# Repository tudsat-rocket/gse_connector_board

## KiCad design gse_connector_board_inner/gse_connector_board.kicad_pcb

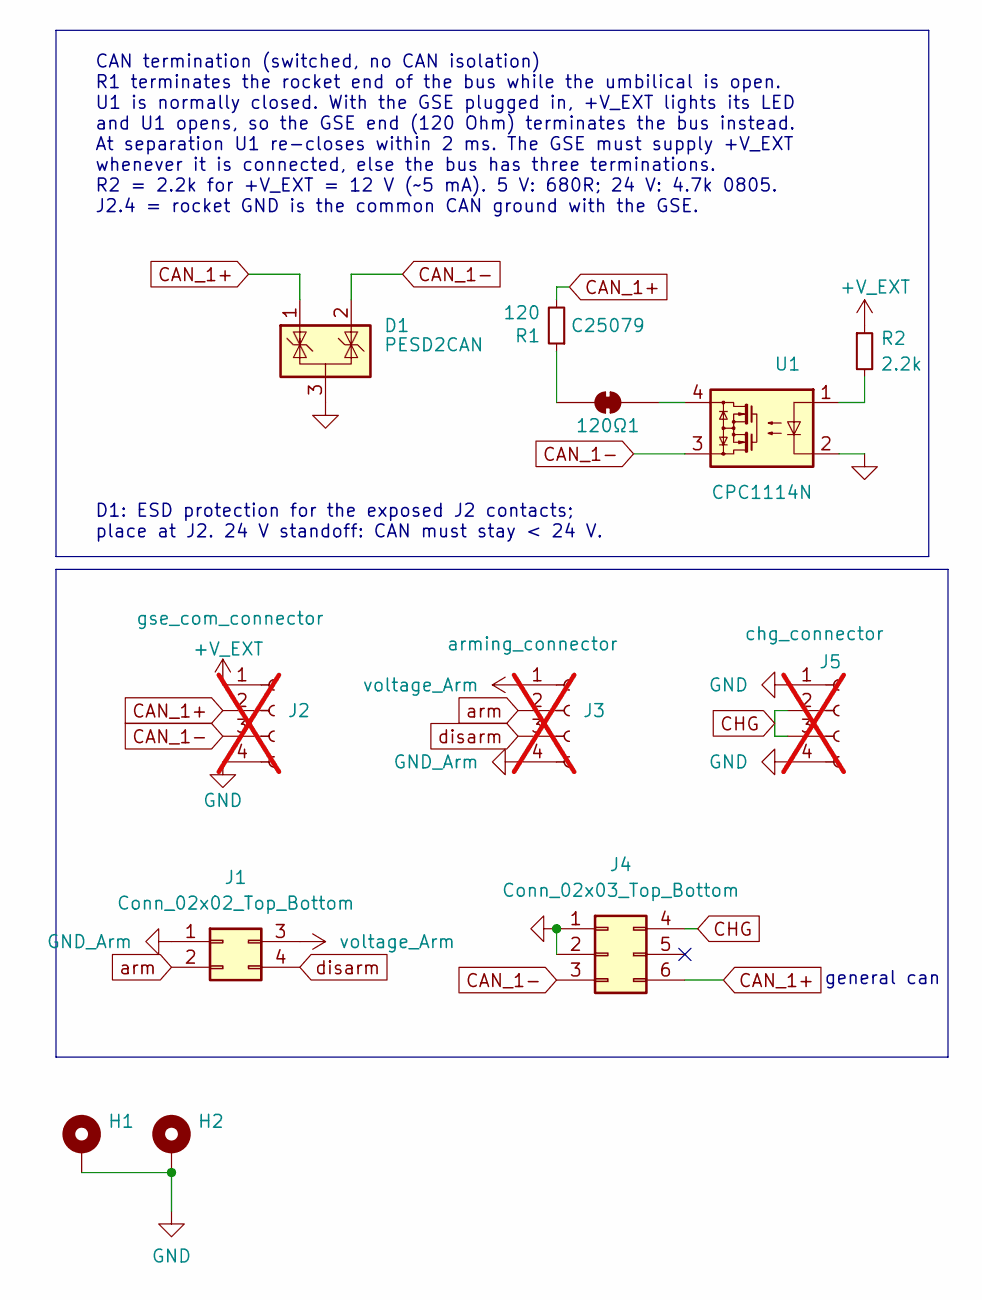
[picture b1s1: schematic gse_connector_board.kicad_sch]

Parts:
120Ω1: SolderJumper_2_Bridged; SolderJumper-2_P1.3mm_Bridged_RoundedPad1.0x1.5mm
D1: PESD2CAN; SOT-23; Part# PESD2CAN,215; LCSC C75176
H1, H2: MountingHole_Pad; MountingHole_3.2mm_M3_DIN965_Pad
J1: Conn_02x02_Top_Bottom; Molex_Micro-Fit_3.0_43045-0400_2x02_P3.00mm_Horizontal
J2: gse_com_connector; 4_pin_mag_con_mv_adapt; not fitted
J3: arming_connector; 4_pin_mag_con_mv_adapt; not fitted
J4: Conn_02x03_Top_Bottom; Molex_Micro-Fit_3.0_43045-0600_2x03_P3.00mm_Horizontal
J5: chg_connector; 4_pin_mag_con_mv_adapt; not fitted
R1: 120; R_0603_1608Metric_Pad0.98x0.95mm_HandSolder; LCSC C25079
R2: 2.2k; R_0603_1608Metric_Pad0.98x0.95mm_HandSolder; LCSC C4190
U1: CPC1114N; SOP-4_3.8x4.1mm_P2.54mm; LCSC C1558975

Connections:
+V_EXT: J2.1, R2.1
CAN_1+: D1.1 (K), J2.2, J4.6, R1.2
CAN_1-: D1.2 (K), J2.3, J4.3, U1.3
CHG: J4.4, J5.2, J5.3
GND: D1.3 (A), H1.1 (1_1), H2.1 (1_1), J2.4, J4.1, J4.2, J5.1, J5.4, U1.2
GND_Arm: J1.1, J3.4
unnamed: 120Ω1.1 (A), R1.1
unnamed: 120Ω1.2 (B), U1.4
unnamed: R2.2, U1.1
arm: J1.2, J3.2
disarm: J1.4, J3.3
voltage_Arm: J1.3, J3.1

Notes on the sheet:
CAN termination (switched, no CAN isolation) R1 terminates the rocket end of the bus while the umbilical is open. U1 is normally closed. With the GSE plugged in, +V_EXT lights its LED and U1 opens, so the GSE end (120 Ohm) terminates the bus instead. At separation U1 re-closes within 2 ms. The GSE 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
general can
D1: ESD protection for the exposed J2 contacts; place at J2. 24 V standoff: CAN must stay < 24 V.

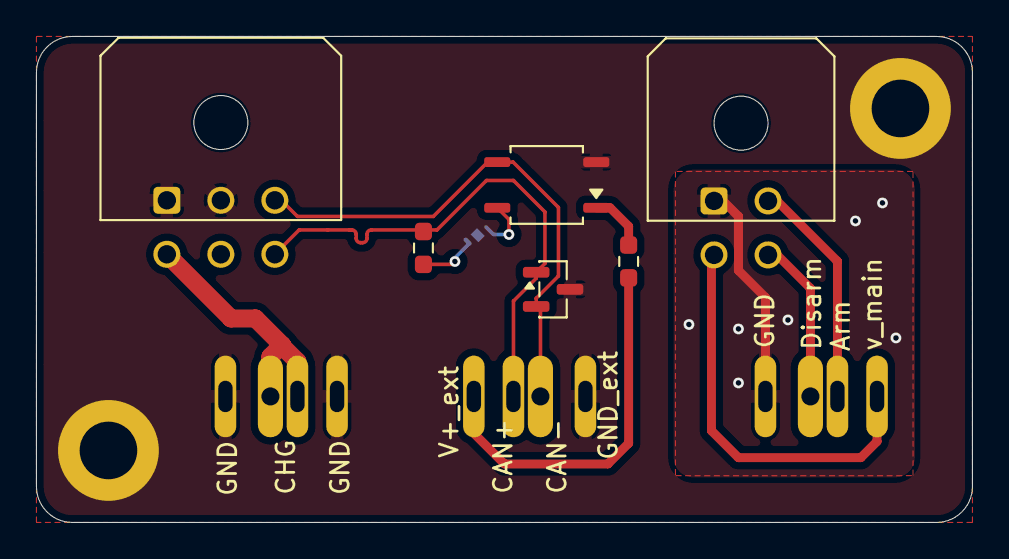
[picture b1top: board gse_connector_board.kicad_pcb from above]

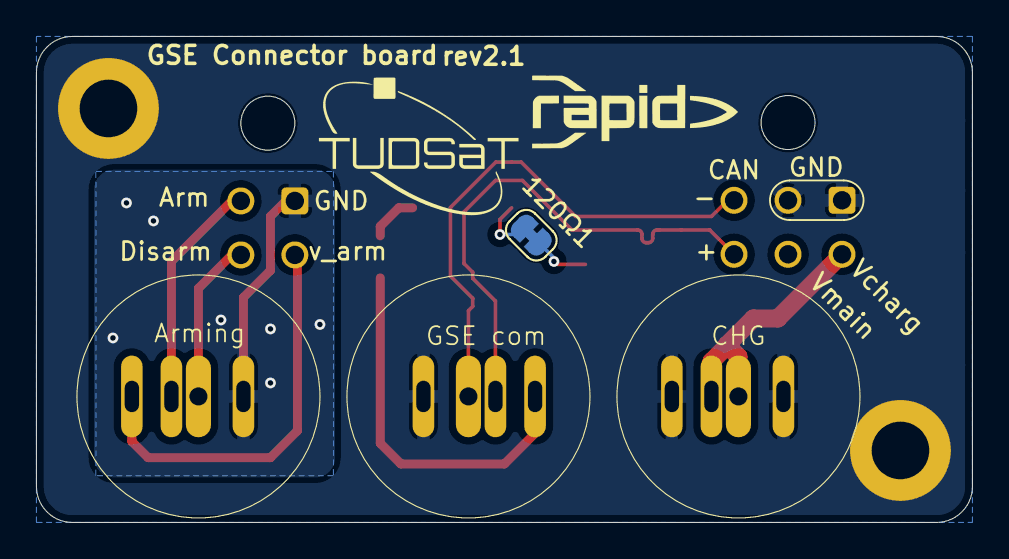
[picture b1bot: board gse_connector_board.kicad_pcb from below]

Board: 2 copper layers, 52.0 x 27.0 mm, 12 parts (4 on the bottom side), 12 nets.

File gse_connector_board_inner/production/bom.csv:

Designator,Footprint,Quantity,Value,LCSC Part #
D1,SOT-23,1,PESD2CAN,C75176
J1,Molex_Micro-Fit_3.0_43045-0400_2x02_P3.00mm_Horizontal,1,Conn_02x02_Top_Bottom,
J4,Molex_Micro-Fit_3.0_43045-0600_2x03_P3.00mm_Horizontal,1,Conn_02x03_Top_Bottom,
R1,0603,1,120,C25079
R2,0603,1,2.2k,C4190
U1,SOP-4_3.8x4.1mm_P2.54mm,1,CPC1114N,C1558975

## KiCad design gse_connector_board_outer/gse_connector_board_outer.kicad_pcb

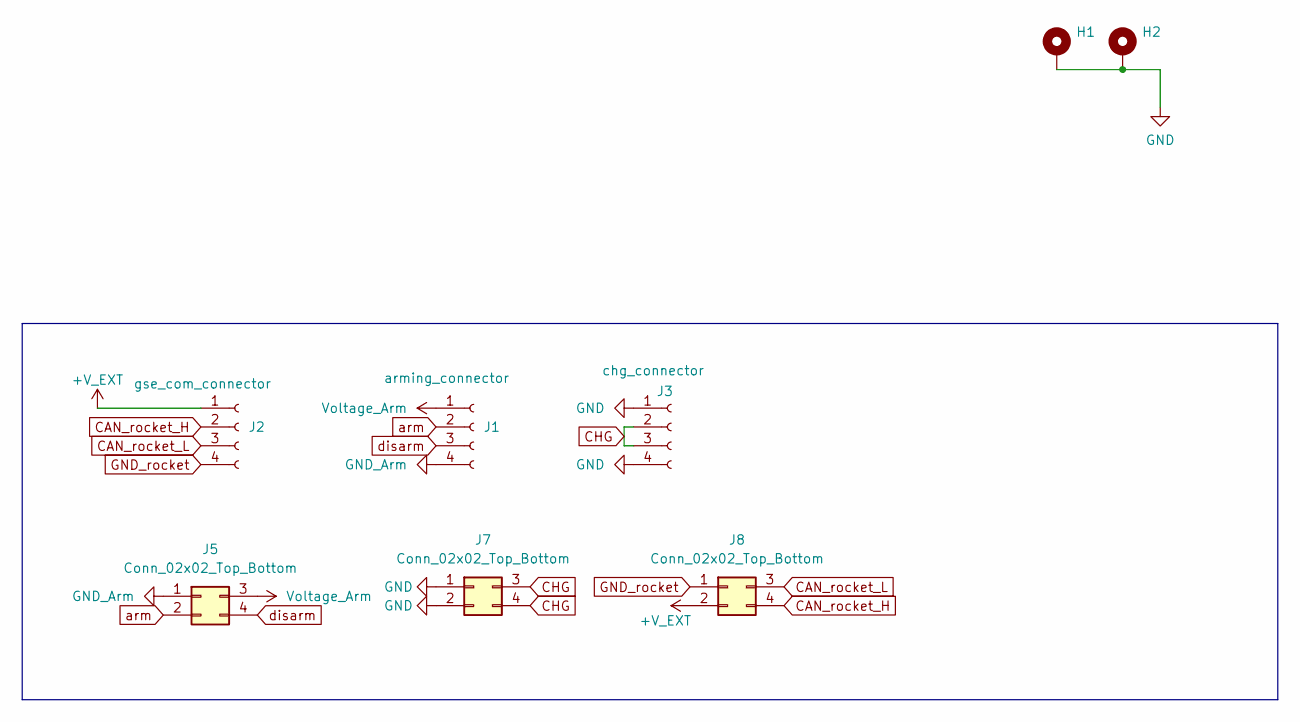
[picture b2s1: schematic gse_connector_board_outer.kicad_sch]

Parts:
H1, H2: MountingHole_Pad; MountingHole_3.2mm_M3_DIN965_Pad
J1: arming_connector; 4_pin_mag_con_flat_mv_adapt
J2: gse_com_connector; 4_pin_mag_con_flat_mv_adapt
J3: chg_connector; 4_pin_mag_con_flat_mv_adapt
J5, J7, J8: Conn_02x02_Top_Bottom; Molex_Micro-Fit_3.0_43045-0400_2x02_P3.00mm_Horizontal

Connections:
+V_EXT: J2.1, J8.2
CAN_rocket_H: J2.2, J8.4
CAN_rocket_L: J2.3, J8.3
CHG: J3.2, J3.3, J7.3, J7.4
GND: H1.1 (1_1), H2.1 (1_1), J3.1, J3.4, J7.1, J7.2
GND_Arm: J1.4, J5.1
GND_rocket: J2.4, J8.1
Voltage_Arm: J1.1, J5.3
arm: J1.2, J5.2
disarm: J1.3, J5.4

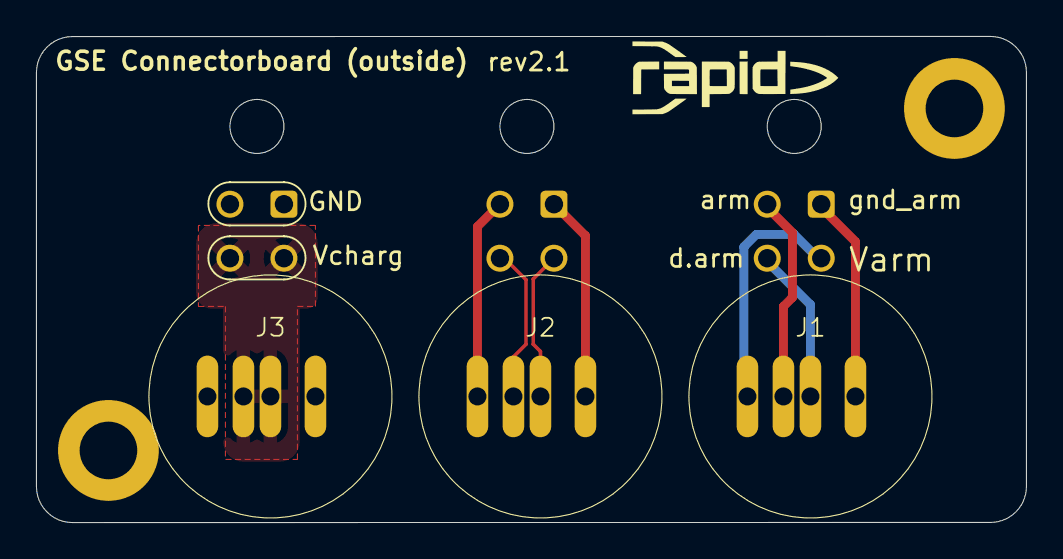
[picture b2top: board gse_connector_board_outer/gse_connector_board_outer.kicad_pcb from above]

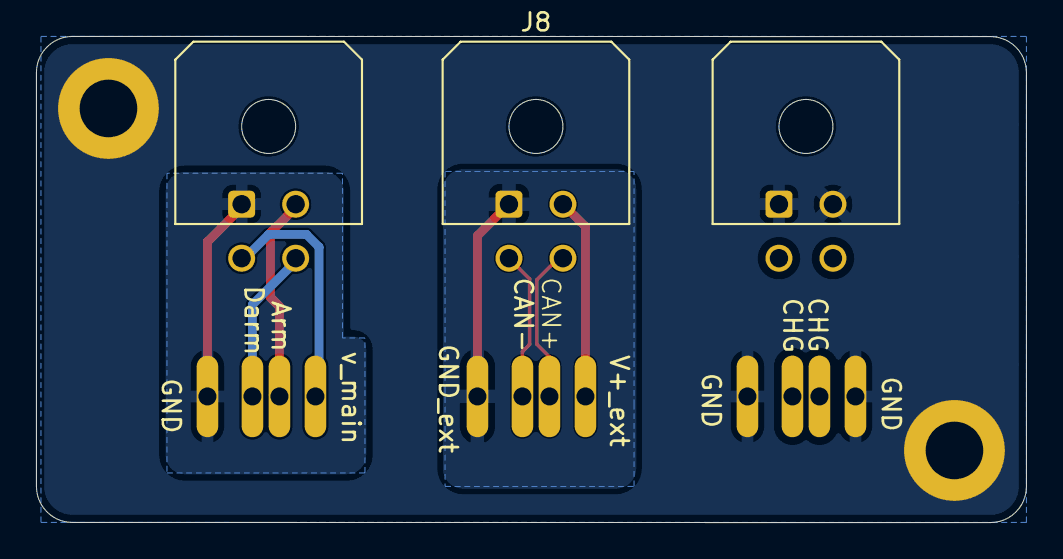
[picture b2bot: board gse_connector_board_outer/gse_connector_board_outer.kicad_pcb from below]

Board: 2 copper layers, 55.0 x 27.0 mm, 8 parts (3 on the bottom side), 10 nets.

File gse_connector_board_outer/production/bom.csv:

Designator,Footprint,Quantity,Value,LCSC Part #
J1,4_pin_mag_con_flat_mv_adapt,1,arming_connector,
J2,4_pin_mag_con_flat_mv_adapt,1,gse_com_connector,
J3,4_pin_mag_con_flat_mv_adapt,1,chg_connector,
"J5, J7, J8",Molex_Micro-Fit_3.0_43045-0400_2x02_P3.00mm_Horizontal,3,Conn_02x02_Top_Bottom,

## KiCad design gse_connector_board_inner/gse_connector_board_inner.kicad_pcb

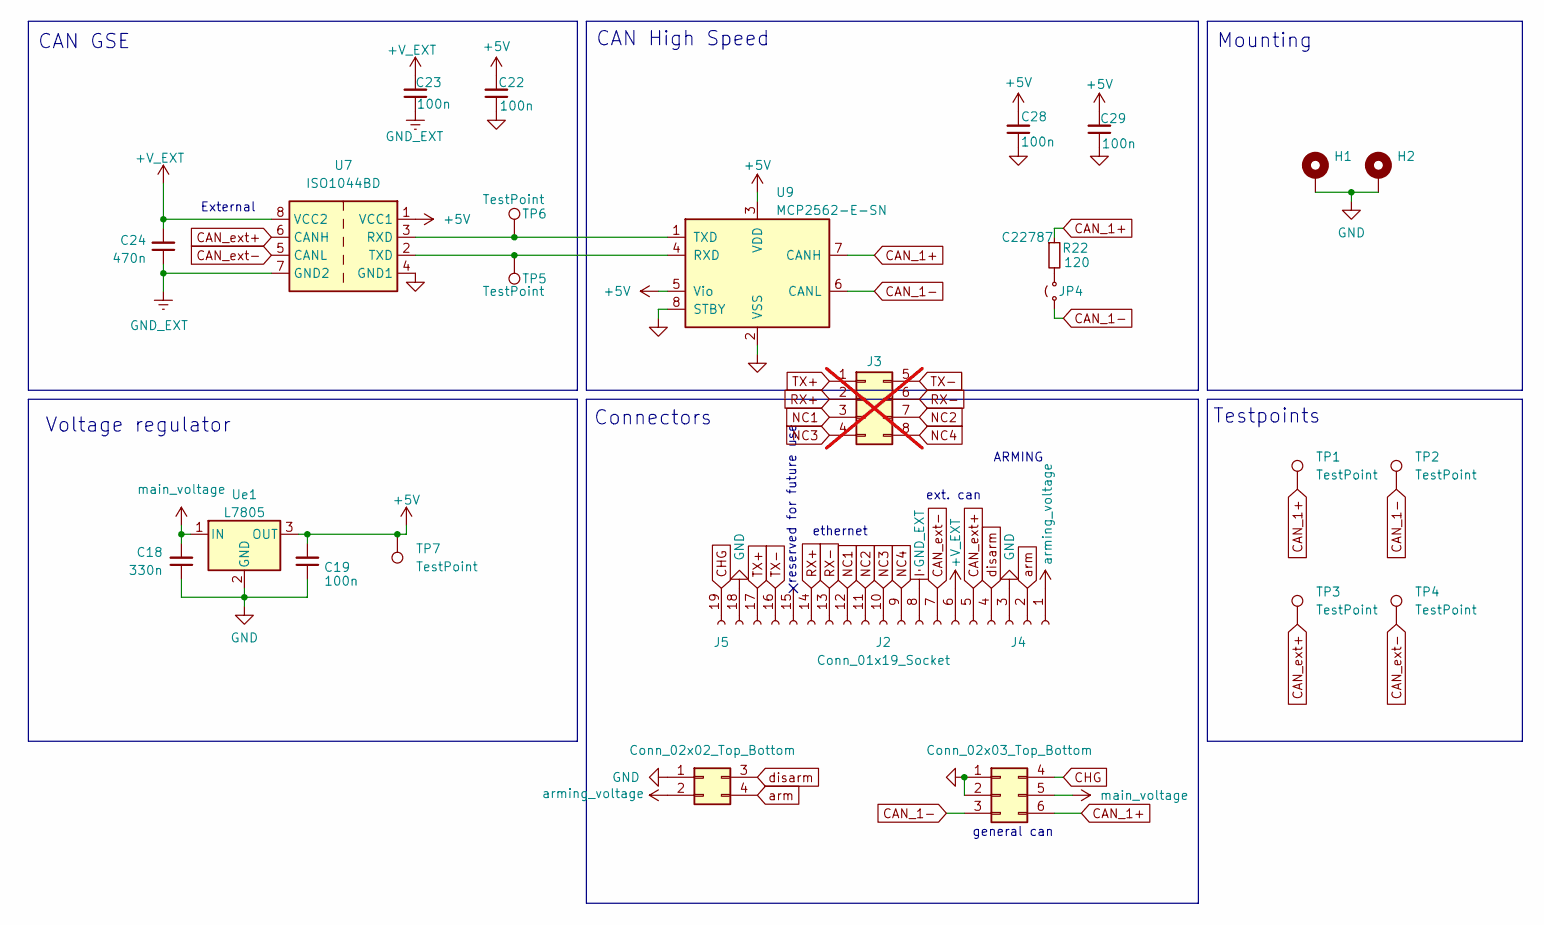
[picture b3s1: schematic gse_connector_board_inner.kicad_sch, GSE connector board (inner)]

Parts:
C18: 330n; C_0603_1608Metric_Pad1.08x0.95mm_HandSolder; Part# CL10B334KO8NNNC; LCSC# C159798
C19: 100n; C_0603_1608Metric_Pad1.08x0.95mm_HandSolder; Part# CL10B104KB8NNNC; LCSC# C1591
C22, C23, C28, C29: 100n; C_0603_1608Metric_Pad1.08x0.95mm_HandSolder; LCSC# C14663
C24: 470n; C_0603_1608Metric_Pad1.08x0.95mm_HandSolder; LCSC# C14663
H1, H2: MountingHole_Pad; MountingHole_3.2mm_M3_DIN965_Pad
J2: Conn_01x19_Socket; tudsat_gse_connector_rev_1
J3: Molex_Micro-Fit_3.0_43045-0800_2x04_P3.00mm_Horizontal; not fitted
J4: Conn_02x03_Top_Bottom; Molex_Micro-Fit_3.0_43045-0600_2x03_P3.00mm_Horizontal
J5: Conn_02x02_Top_Bottom; Molex_Micro-Fit_3.0_43045-0400_2x02_P3.00mm_Horizontal
JP4: Jumper_2_Small_Open; SolderJumper-2_P1.3mm_Bridged_RoundedPad1.0x1.5mm
R22: 120; R_0603_1608Metric_Pad0.98x0.95mm_HandSolder; LCSC C22787
TP1, TP2, TP3, TP4, TP5, TP6, TP7: TestPoint; TestPoint_Pad_D1.0mm
U7: ISO1044BD; SOIC-8_3.9x4.9mm_P1.27mm; LCSC# C2878198
U9: MCP2562-E-SN; SOIC-8_3.9x4.9mm_P1.27mm; Part# MCP2562T-E/SN; LCSC# C191417
Ue1: L7805; TO-252-2; Part# L7805CDT-TR; LCSC C310413

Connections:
+5V: C19.2, C22.2, C28.2, C29.2, TP7.1 (1_1), U7.1 (VCC1), U9.3 (VDD), U9.5 (Vio), Ue1.3 (OUT)
+V_EXT: C23.2, C24.2, J2.6, U7.8 (VCC2)
CAN_1+: J4.6, R22.1, TP1.1 (1_1), U9.7 (CANH)
CAN_1-: J4.3, JP4.1 (A), TP2.1 (1_1), U9.6 (CANL)
CAN_ext+: J2.5, TP3.1 (1_1), U7.6 (CANH)
CAN_ext-: J2.7, TP4.1 (1_1), U7.5 (CANL)
CHG: J2.19, J4.4
GND: C18.1, C19.1, C22.1, C28.1, C29.1, H1.1 (1_1), H2.1 (1_1), J2.3, J2.18, J4.1, J4.2, J5.1, U7.4 (GND1), U9.2 (VSS), U9.8 (STBY), Ue1.2 (GND)
GND_EXT: C23.1, C24.1, J2.8, U7.7 (GND2)
NC1: J2.12, J3.3
NC2: J2.11, J3.7
NC3: J2.10, J3.4
NC4: J2.9, J3.8
unnamed: JP4.2 (B), R22.2
unnamed: TP6.1 (1_1), U7.3 (RXD), U9.1 (TXD)
unnamed: TP5.1 (1_1), U7.2 (TXD), U9.4 (RXD)
RX+: J2.14, J3.2
RX-: J2.13, J3.6
TX+: J2.17, J3.1
TX-: J2.16, J3.5
arm: J2.2, J5.4
arming_voltage: J2.1, J5.2
disarm: J2.4, J5.3
main_voltage: C18.2, J4.5, Ue1.1 (IN)

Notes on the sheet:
Testpoints
Mounting
Connectors
CAN GSE
External
general can
ARMING
Voltage regulator
ext. can
CAN High Speed
ethernet
reserved for future use

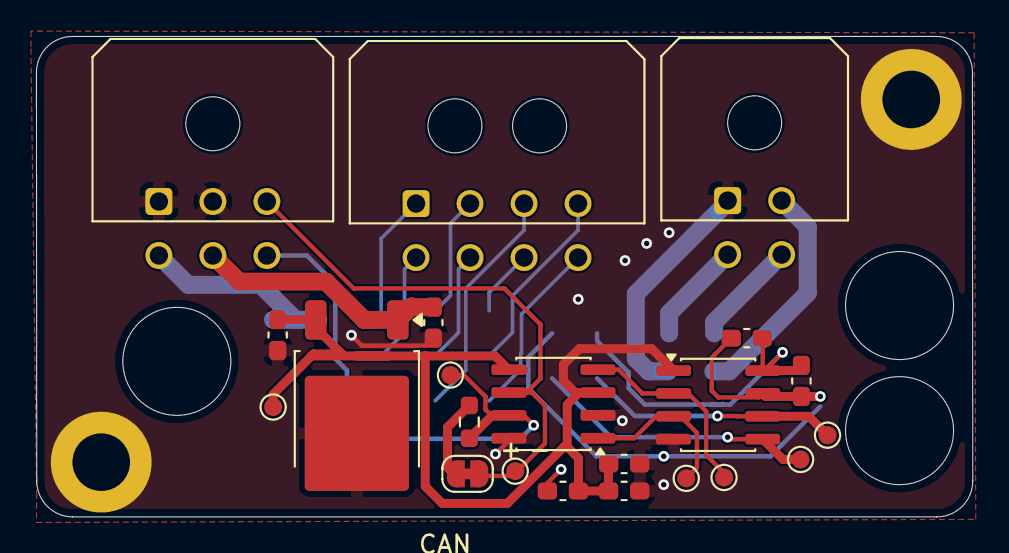
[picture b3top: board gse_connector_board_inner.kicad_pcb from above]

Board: 2 copper layers, 52.0 x 26.7 mm, 25 parts (1 on the bottom side), 24 nets.

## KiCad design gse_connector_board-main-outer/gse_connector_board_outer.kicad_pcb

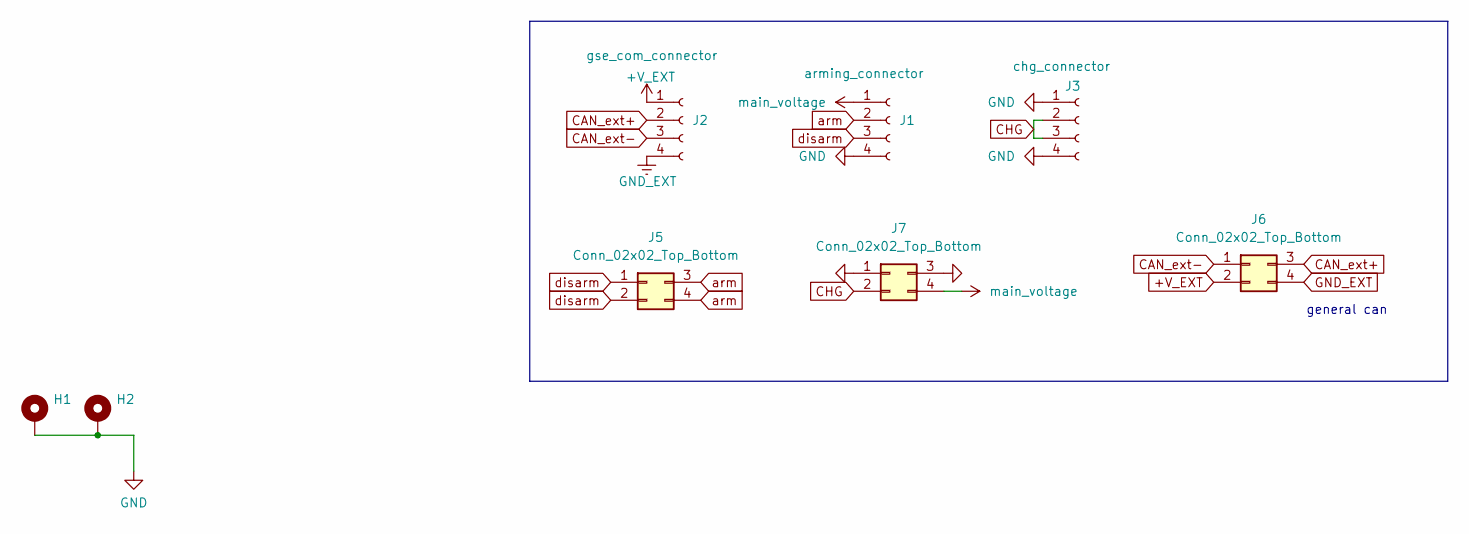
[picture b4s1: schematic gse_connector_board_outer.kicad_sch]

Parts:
H1, H2: MountingHole_Pad; MountingHole_3.2mm_M3_DIN965_Pad
J1: arming_connector; 4_pin_mag_con_new
J2: gse_com_connector; 4_pin_mag_con_new
J3: chg_connector; 4_pin_mag_con_new
J5, J6, J7: Conn_02x02_Top_Bottom; Molex_Micro-Fit_3.0_43045-0400_2x02_P3.00mm_Horizontal

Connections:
+V_EXT: J2.1, J6.2
CAN_ext+: J2.2, J6.3
CAN_ext-: J2.3, J6.1
CHG: J3.2, J3.3, J7.2
GND: H1.1 (1_1), H2.1 (1_1), J1.4, J3.1, J3.4, J7.1, J7.3
GND_EXT: J2.4, J6.4
arm: J1.2, J5.3, J5.4
disarm: J1.3, J5.1, J5.2
main_voltage: J1.1, J7.4

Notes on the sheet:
general can

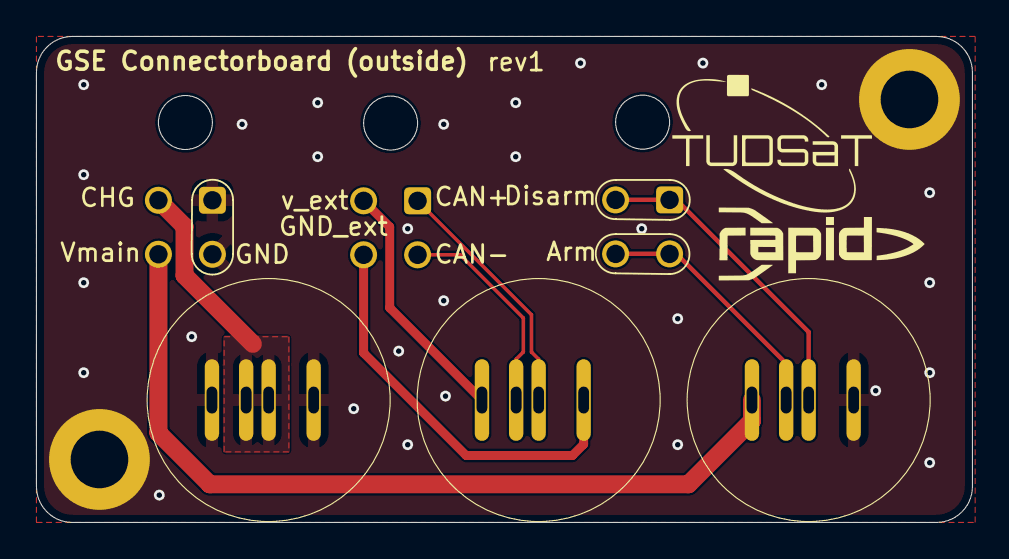
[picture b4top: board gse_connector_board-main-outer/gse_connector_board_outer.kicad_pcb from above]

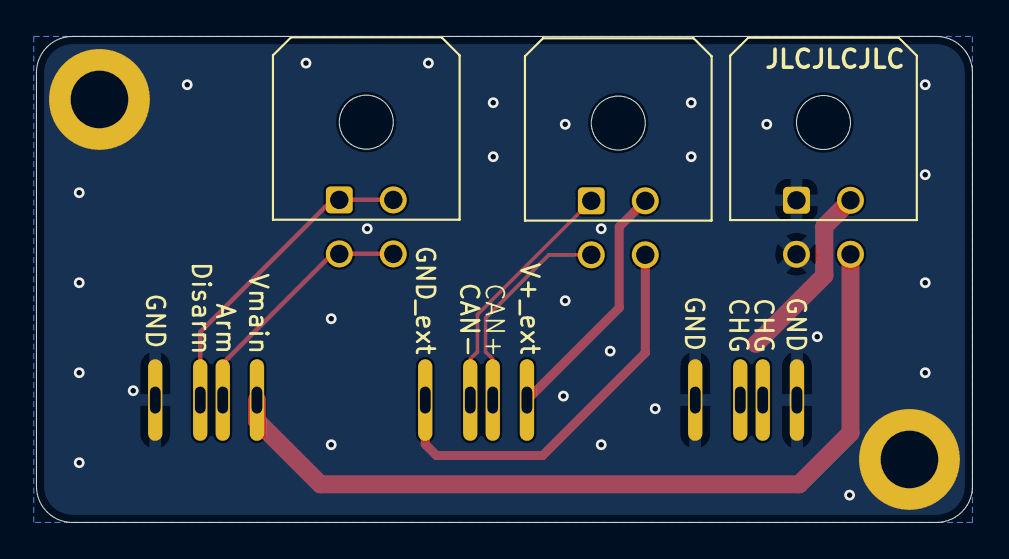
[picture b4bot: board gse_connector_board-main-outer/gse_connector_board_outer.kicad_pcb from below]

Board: 2 copper layers, 52.0 x 27.0 mm, 8 parts (3 on the bottom side), 9 nets.

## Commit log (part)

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2026-05-17 init
2026-06-22 Add files via upload
    changed footprint of agnetic connector, finished routing and layout of connector board
2026-06-23 Add files via upload
    added rounded corners
2026-06-24 Add files via upload
    Added Silkscreen and Testpoints for CAN
2026-06-24 Add files via upload
    excluded Molex connectors from BOM and put in DNP.
    added Testpoints for 5V, main voltage and Charging
2026-06-24 Add files via upload
    changed silkscreen
2026-06-24 Add files via upload
    added the outsidepart of the connector
2026-06-25 final silkscreen improvements and small fixes
2026-06-27 fix silkscreen
2026-06-28 edited grounding and edge cuts
2026-06-28 some changes
2026-06-29 order version
